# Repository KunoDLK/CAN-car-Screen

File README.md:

# Car Dashboard LCD Display

## Overview
A project to develop a car dashboard display using an LCD screen and microcontroller, featuring gauge displays and various connectivity options.

Arduino powder display that will display car data over CAN on to a TFT Display

---

## System Architecture
- **Microcontroller**: STM32 F4 (might be okay with lower grade of MCU)
- **LCD Screen**: Specifications and resolution
  - 7 inch 800x480 TFT panel w/ 40 pin ribbon connection
- **Power Supply**: Details on how the system is powered
  - Usb-C, standard 5v 500mA might be okay for power beget however we might need to think about more power depending on  

---

## Software Design
- **Current Structure**: Overview of existing code.
  - Threads:
    - Display Thread:
      - Drawing to the screen
      - Buffering draw calls
      - Managing the display layers
    - CAN massage thread
      - Receives can bus frames and enqueue them
      - Filter out invalid data
    - Gauge drawing:
      - Updates dynamic UI elements by firing draw calls
    - USB communication:
      - handles communication with host PC

- **Refactoring Plan**: How we’ll improve scalability and configurability.

---

## Hardware Specifications
- **Components**: Microcontroller, LCD, EEPROM 
- **Connections**:
  - CAN bus
  - WinUSB (USB connection)
  - Parallel connection to LCD driver

Using:
https://github.com/sumotoy/RA8875 for display driver (Currently included in arduino IDE)

Using:
https://github.com/autowp/arduino-mcp2515 for CAN driver

---

## User Interface
- **Gauge Display**: Layout and design.
Something like this

- **Interactivity**: Any interactive elements.

---

## Communication Interfaces
- **CAN Bus**: Integration details.
- **USB**: WinUSB specifics.
- **Parallel Connection**: Interface with LCD driver.

---

## Mechanical Design
- **3D Model**: CAD design process.
- **3D Printing**: Materials and specifications.
- **Mounting**: Attaching the case to the dashboard.

---

## Software Architecture
- **RTOS Kernel**: Overview of FreeRTOS.
- **Task Management**: Structuring and prioritisation.

---

## Testing and Validation
- **Methodology**: How we’ll ensure functionality and reliability.

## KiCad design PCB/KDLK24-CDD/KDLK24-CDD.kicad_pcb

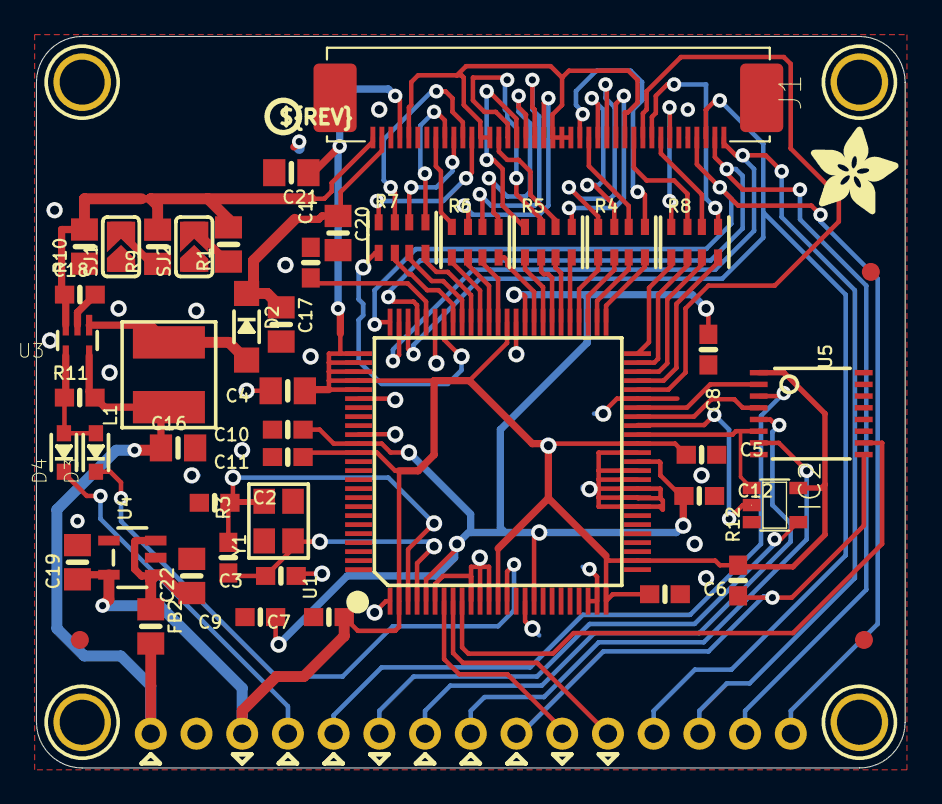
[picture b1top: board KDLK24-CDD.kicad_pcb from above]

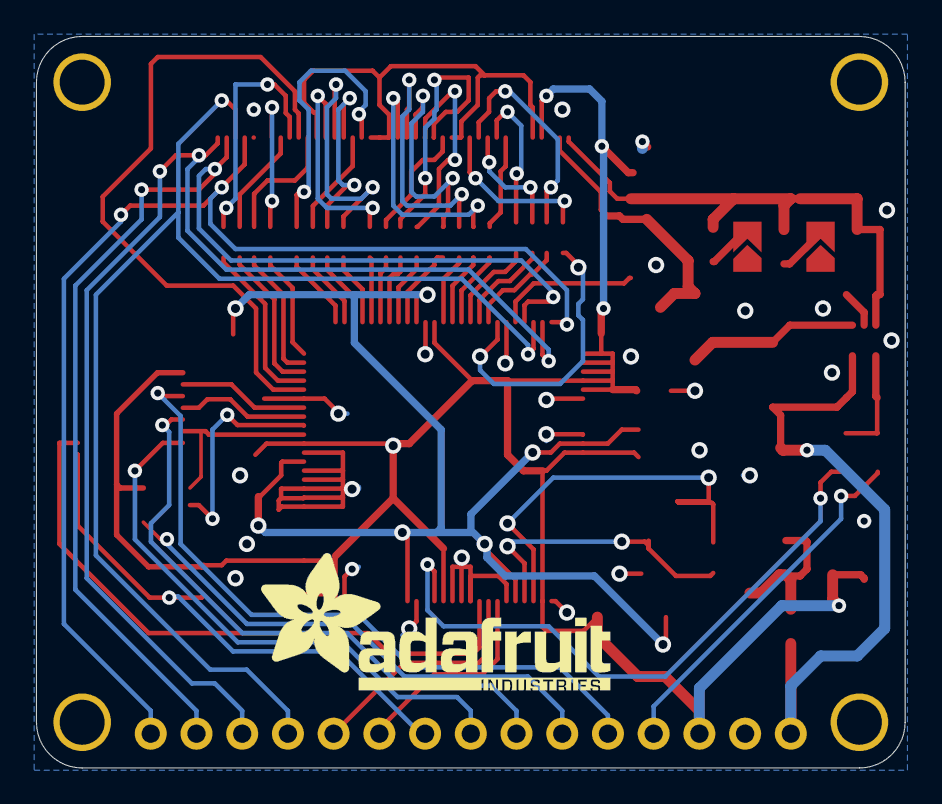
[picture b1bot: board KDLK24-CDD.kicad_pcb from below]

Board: 2 copper layers, 48.3 x 40.6 mm, 79 parts (4 on the bottom side), 73 nets.

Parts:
C1, C5, C6, C7, C8, C9, C10, C11, C12, C18: 0.1uF; 0603-NO
C2, C3: 15pF; 0603-NO
C4, C17, C20: 1uF; 0805-NO
C16, C19, C21, C22: 10uF; 0805-NO
D2: MBR0540; SOD-123
D3, D4: 1N4148; SOD-323_MINI
FB2: Ferrite; 0805-NO
FID1, FID2, FID3: FIDUCIAL_1MM
IC2: 74AHC1G125DBV; SOT23-5
J1: 40PINFPC_GENERIC; FPC_40
JP1: Breakout; 1X15-CB
L1: 6.8uH large inductor; INDUCTOR_5X5MM_NR5040_NOTHERMALS
PLABEL0: PLABEL0
PLABEL1: PLABEL1
PLABEL2: PLABEL2
PLABEL3: PLABEL3
PLABEL4: PLABEL4
PLABEL5: PLABEL5
PLABEL6: PLABEL6
PLABEL7: PLABEL7
PLABEL8: PLABEL8
PLABEL9: PLABEL9
PLABEL10: PLABEL10
PLABEL11: PLABEL11
PLABEL12: PLABEL12
PLABEL13: PLABEL13
PLABEL14: PLABEL14
PLABEL15: PLABEL15
PLABEL16: PLABEL16
PLABEL17: PLABEL17
PLABEL18: PLABEL18
PLABEL19: PLABEL19
PLABEL20: PLABEL20
PLABEL21: PLABEL21
PLABEL22: PLABEL22
PLABEL23: PLABEL23
R1: 2Ω; 0805-NO
R3: 1M; 0603-NO
R4, R5, R6, R7, R8: 33; RESPACK_4X0603
R9, R10: 8.2Ω; 0805-NO
R11, R12: 10K; 0603-NO
SJ1: +25mA; SOLDERJUMPER_ARROW_NOPASTE
SJ2: +100mA; SOLDERJUMPER_ARROW_NOPASTE
U1: RA8875; LQFP100
U3: TPS61169; SC70-5
U4: AP2127K-3.3; SOT23-5
U5: 74HC4050; TSSOP16
U$18: ADAFRUIT_5MM
U$21, U$22, U$23, U$24: MOUNTINGHOLE2.5; MOUNTINGHOLE_2.5_PLATED
U$25: ADAFRUIT_TEXT_20MM
U$30: PCBFEAT-REV-040
Y1: 20MHz; CRYSTAL_3.2X2.5

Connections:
1.5V: C8.1, C9.1, C10.1, C12.1, U1.5, U1.17, U1.38, U1.60, U1.86
+3V3: C4.1, C5.1, C6.1, C7.1, C11.1, C19.1, C21.1, IC2.5, J1.4, JP1.13, R12.2, U1.2, U1.13, U1.25, U1.27, U1.40, U1.62, U1.76, U1.77, U1.78, U1.79, U1.80, U1.87, U4.5, U5.1
+24V: C17.1, C20.1, D2.C, J1.2
B3: J1.24, R4.5
B4: J1.25, R4.6
B5: J1.26, R4.7
B6: J1.27, R4.8
B7: J1.28, R5.5
BACKLITE: D4.C, JP1.12
CS: JP1.8, U5.7
DE: J1.34, R8.8
G2: J1.15, R5.6
G3: J1.16, R5.7
G4: J1.17, R5.8
G5: J1.18, R6.5
G6: J1.19, R6.6
G7: J1.20, R6.7
GND: C1.2, C2.1, C3.1, C4.2, C5.2, C6.2, C7.2, C8.2, C9.2, C10.2, C11.2, C12.2, C16.2, C17.2, C18.2, C19.2, C20.2, C21.2, C22.2, IC2.3, J1.3, J1.5, J1.6, J1.7, J1.13, J1.14, J1.21, J1.22, J1.23, J1.29, J1.36, JP1.14, R10.1, SJ1.1, SJ2.1, U1.1, U1.6, U1.10, U1.11, U1.12, U1.16, U1.23, U1.24, U1.26, U1.28, U1.33, U1.34, U1.35, U1.36, U1.37, U1.39, U1.45, U1.61, U1.70, U1.81, U1.85, U3.2, U4.2, U5.8
HSYNC: J1.32, R8.5
INT: JP1.5, U1.8
LEDK: C18.1, J1.1, R1.2, R9.2, R10.2, U3.3
MISO: IC2.4, JP1.10
MOSI: JP1.9, U5.5
MOSI_3V: U1.43, U5.4
unnamed: D2.A, L1.P$2, U3.1
unnamed: C2.2, R3.2, U1.3, Y1.2
unnamed: C1.1, U1.71
unnamed: R4.4, U1.51
unnamed: R4.3, U1.52
unnamed: R4.2, U1.53
unnamed: R4.1, U1.54
unnamed: R5.4, U1.55
unnamed: R5.3, U1.56
unnamed: R5.2, U1.57
unnamed: R5.1, U1.58
unnamed: R6.4, U1.59
unnamed: R6.3, U1.63
unnamed: R6.2, U1.64
unnamed: R6.1, U1.65
unnamed: R7.4, U1.66
unnamed: R7.3, U1.67
unnamed: R7.2, U1.68
unnamed: R7.1, U1.69
unnamed: R8.1, U1.50
unnamed: R8.2, U1.49
unnamed: R8.3, U1.48
unnamed: R8.4, U1.47
unnamed: R9.1, SJ1.2
unnamed: C22.1, FB2.1, U4.1, U4.3
unnamed: R1.1, SJ2.2
unnamed: C3.2, R3.1, U1.4, Y1.1
ON/OFF: J1.31, U1.46
PIXCLK: J1.30, R8.7
PWM0: D3.C, U1.14
R3: J1.8, R6.8
R4: J1.9, R7.5
R5: J1.10, R7.6
R6: J1.11, R7.7
R7: J1.12, R7.8
RA_MISO: IC2.2, U1.42
RESET: JP1.7, R12.1, U5.9
RESET_3V: U1.9, U5.10
SCK: JP1.11, U5.3
SHDN: D3.A, D4.A, R11.1, U3.4
SPI_CLK_3V: U1.44, U5.2
SPI_CS_3V: IC2.1, U1.41, U5.6
VIN: C16.1, FB2.2, JP1.15, L1.P$1, R11.2, U3.5
VSYNC: J1.33, R8.6
WAIT: JP1.6, U1.7
X+: J1.37, JP1.1, U1.75
X-: J1.39, JP1.2, U1.72
Y+: J1.38, JP1.4, U1.73
Y-: J1.40, JP1.3, U1.74

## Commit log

2023-03-23 Update issue templates
2023-03-23 added macros for UIType
2023-03-27 added serial config loop, started to fix barographs
    need to make barographs to add or remove a signal rectangle a frame to optimise performance and add smoothing
2023-03-27 fixed conflict
2023-03-27 Fixed Barograph array
2024-10-24 Imported Breakout board from Adafruit
2024-10-24 removed local files to add sub module
2024-10-24 imported Adafruit driver repo
2024-10-24 Imported project from Adafruit repo
2024-10-24 Added rule to ignore the file locks
2024-10-24 Switched to use the standard gitignore for KICAD project. will most likely need to merge with cmake/c when software starts
2024-10-24 Imported project from Adafruit repo, again.... (;
2024-10-24 Added project symbol lib
2024-10-24 started creating schematic from layout
2024-10-24 Completed schematic import
2024-10-31 got the bars working
2024-11-01 Height was incorrect for the bars
2024-11-01 removed debug output on to screen
2024-11-01 changed FPS to use floating point arithmetic
2024-11-01 change number of noduals
2024-11-15 Added display repo
2024-11-15 Update Readme for peer programming.
